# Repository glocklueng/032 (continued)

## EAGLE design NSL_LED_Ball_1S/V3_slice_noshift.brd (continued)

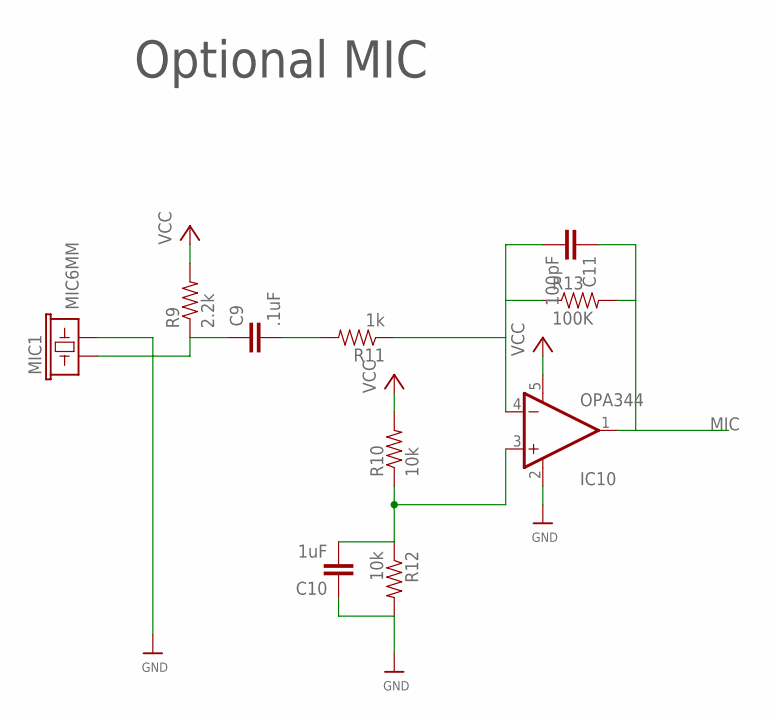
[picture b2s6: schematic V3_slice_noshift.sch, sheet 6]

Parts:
C9: .1uF; 0805
C10: 1uF; 0805
C11: 100pF; 0805
IC10: OPA344; SOT23-5
MIC1: MIC6MM; MIC-6MM
R9: 2.2k; 0805
R10, R12: 10k; 0805
R11: 1k; 0805
R13: 100K; 0805

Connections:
GND: C10.1, IC10.2 (V-), MIC1.2, R12.2; also elsewhere on the board
MIC: C11.1, IC10.1 (OUT), R13.2; also elsewhere on the board
unnamed: C9.2, R11.2
unnamed: C11.2, IC10.4 (-IN), R11.1, R13.1
unnamed: C9.1, MIC1.1, R9.1
unnamed: C10.2, IC10.3 (+IN), R10.1, R12.1
VCC: IC10.5 (V+), R9.2, R10.2; also elsewhere on the board

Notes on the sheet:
Optional MIC

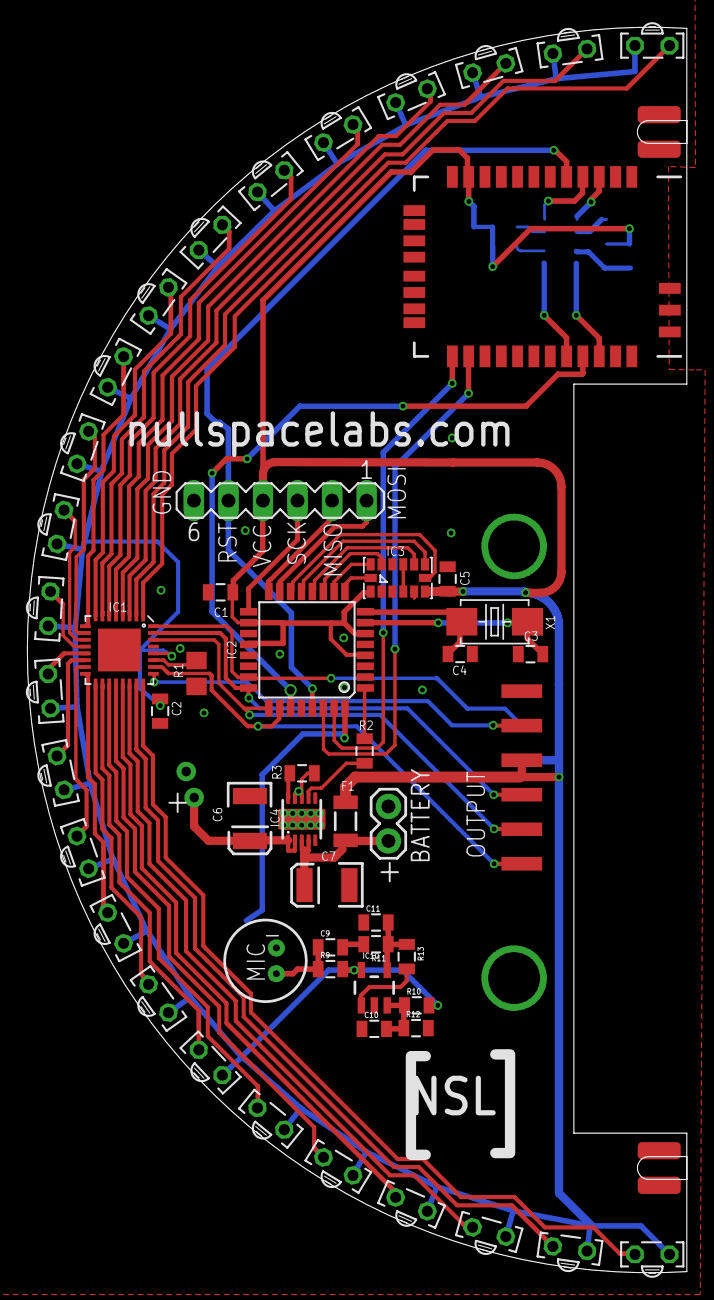
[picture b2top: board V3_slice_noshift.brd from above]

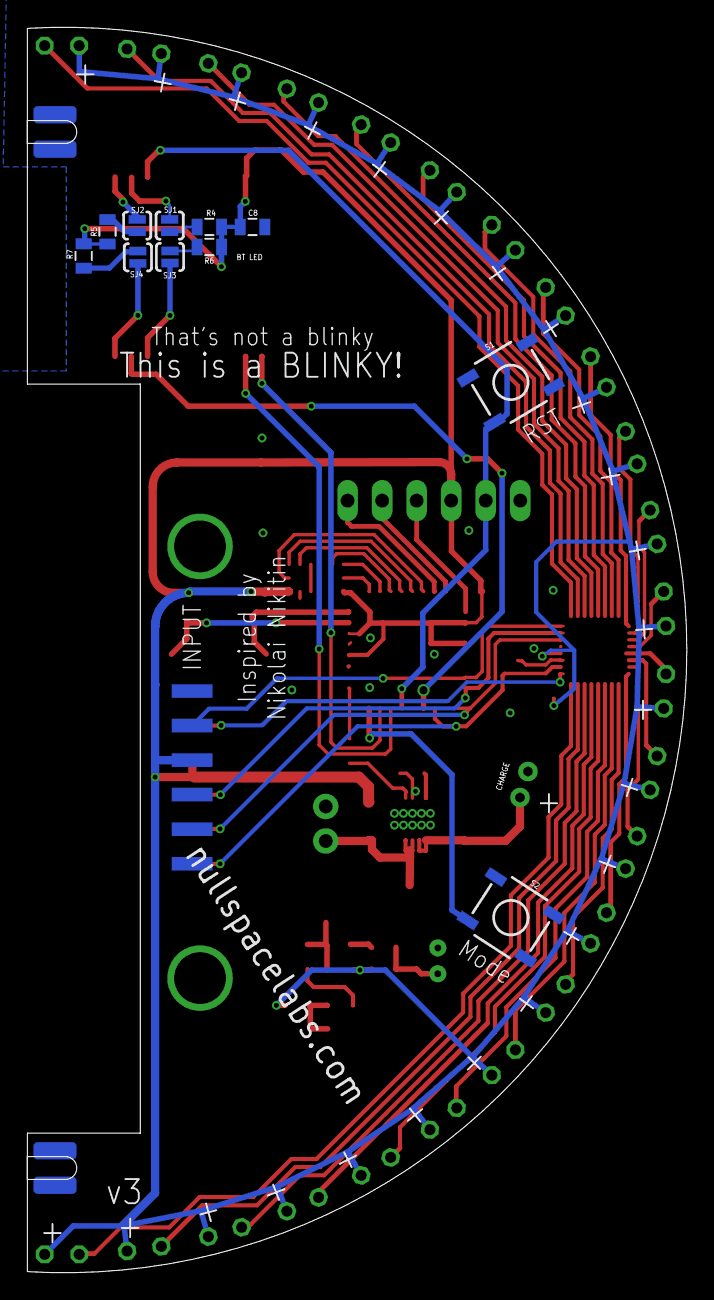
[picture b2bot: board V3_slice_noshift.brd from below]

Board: 2 copper layers, 48.5 x 91.6 mm, 69 parts (13 on the bottom side), 66 nets.

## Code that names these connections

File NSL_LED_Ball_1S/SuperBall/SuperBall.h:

#ifndef _RF_BLINKY_H_
#define _RF_BLINKY_H_ ( 1 )

// includes

#include <avr/io.h>
#include <util/delay.h>
#include <avr/interrupt.h>
#include <avr/sfr_defs.h>


#include <math.h> 
#include <avr/eeprom.h>
#include <avr/sleep.h>
#include <avr/power.h>
#include <avr/pgmspace.h>

#include <stdlib.h>
#include <string.h>

#include <math.h>


// typedefs

typedef unsigned char uchar;
typedef unsigned int uint;

// structures

// defines

#define SUPERBALL_WIDTH			(24)
#define SUPERBALL_HEIGHT		(16)

#define NUM_TLC5947 ( 16 )

#define bit_set(reg, bit) reg |= 1 << bit 
#define bit_clr(reg, bit) reg &= ~(1 << bit) 

#define SWSPI_PORT PORTD
#define SWSPI_DIR  DDRD
#define SWSPI_IN   PIND

#ifndef TWO_PI
#define TWO_PI 				( 6.283185307f )
#endif

#define SWSPI_SS   (1<<1) // (CSn of the SPI can also be connected to GND permanently.) 
#define SWSPI_SCK  (1<<2)  // CLK  SCL/SPC clock signal 
#define SWSPI_MOSI (1<<4)  // mosi sda/sdi/sdo master out,slave in PD2 
#define SWSPI_MISO (1<<4)  // miso SDO



#define DATPORT PORTC
#define CLKPORT PORTC //pc1
#define LATPORT PORTC
#define DATDDR DDRC

#define DATPIN PC0	//	SIN
#define CLKPIN PC1
#define BLANKPIN PC2
#define LATPIN PC3

#define SIN_PIN		_BV( PC0 ) /// PC0
#define SCLK_PIN	_BV( PC1 ) /// PC1
#define BLANK_PIN	_BV( PC2 )    /// PC2
#define XLAT_PIN	_BV( PC3 ) /// PC3


extern uint16_t LEDChannels[(NUM_TLC5947*24)];
extern unsigned char brightnessShift;
extern int gCount;

// prototypes

void USART_init(void);
unsigned char USART_receive(void);
void USART_send( unsigned char data);
void USART_putstring(char* StringPtr);
void SetPoint( unsigned short x, unsigned short y,unsigned short val);
void Clear(unsigned short val);
void Line( int x,int y,int x1,int y1);
void sleep_down( void );

// TLC
void WriteLEDArray(unsigned int count);
void LEDscan(int red, float degreeoffset,unsigned int count);
void LEDscan2(int red, float degreeoffset,unsigned int count);
void LEDscan3(int red, float degreeoffset,unsigned int count);
void LED_Init(void);
void LEDscan2Add(int red, float degreeoffset,unsigned int count);

//sw spi
void SWSPI_init();
void SWSPI_write( uint8_t address, uint8_t value );
uint8_t SWSPI_read( uint8_t address );




#endif

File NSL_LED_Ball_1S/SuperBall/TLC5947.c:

#include "SuperBall.h"


// Modified version of Garrett's octobrite code


// For octobrite code


uint16_t LEDChannels[(NUM_TLC5947*24)];

void SetPoint( unsigned short x, unsigned short y,unsigned short val)
{
	LEDChannels[ (  x * SUPERBALL_WIDTH ) + ( SUPERBALL_HEIGHT - y ) ] = val;
}

// 0.4095
void Clear(unsigned short val)
{

    for(unsigned short LEDindex = 0; LEDindex < (NUM_TLC5947  * 24); LEDindex++)
	{
      LEDChannels[LEDindex] = val;
    }
}

unsigned char brightnessShift= 0;


extern unsigned char chargeMode ;

//------------------------------------------------------------------------------------------
// Read all bits in the LEDChannels array and send them on the selected pins
//------------------------------------------------------------------------------------------
void WriteLEDArray(unsigned int count) {

  unsigned short tempOne = 0;

  for (unsigned int i = 0; i < (count  * 24); i++) {

    tempOne = LEDChannels[i]>>brightnessShift;
	
	// this limits the current draw during charging
	if( chargeMode ){
		tempOne >>= 3;
	}

    for (int j = 0; j < 12; j++) {
      if ((tempOne >> (11 - j)) & 1) {
        DATPORT |= (1 << DATPIN);
      } 
      else {
        DATPORT &= ~(1 << DATPIN);
      }

      CLKPORT |= (1 << CLKPIN);
      CLKPORT &= ~(1 << CLKPIN); 

    } 
  }

  LATPORT |= (1 << LATPIN | 1 << BLANKPIN);
  LATPORT &= ~(1 << LATPIN | 1 << BLANKPIN);
}

//------------------------------------------------------------------------------------------
// Sample function to draw a scanning pattern with fading
//------------------------------------------------------------------------------------------
void LEDscan(int red, float degreeoffset,unsigned int count) 
{

  float brightnessfactor = 0.0f;
  
  float scanindex = (1.0f + sinf(degreeoffset*3.14159f/180.0f)) * ((float)(NUM_TLC5947 * 24 ) / 2.0);
  
    for(unsigned int LEDindex = 0; LEDindex < (NUM_TLC5947  * 24); LEDindex++) {
      

      brightnessfactor = expf(0.0f - fabs(scanindex - ((float)LEDindex + 0.5f)) * 1.3f);

      LEDChannels[LEDindex] = red * brightnessfactor;
    }
    
    WriteLEDArray(count);  
}

void LEDscan2(int red, float degreeoffset,unsigned int count) 
{

  float brightnessfactor = 0.0f;
  
  float scanindex = (1.0f + sinf(degreeoffset*3.14159f/180.0f)) * ((float)(count * 24 ) / 2.0);
  
    for(unsigned int LEDindex = 0; LEDindex < (count  * 24); LEDindex++) {
      

      brightnessfactor = expf(0.0f - fabs(scanindex - ((float)LEDindex + 0.5f)) * 1.3f);

      LEDChannels[LEDindex] = red * brightnessfactor;
    }
}

void LEDscan2Add(int red, float degreeoffset,unsigned int count) 
{

  float brightnessfactor = 0.0f;
  
  float scanindex = (1.0f + sinf(degreeoffset*3.14159f/180.0f)) * ((float)(count * 24 ) / 2.0);
  
    for(unsigned int LEDindex = 0; LEDindex < (count  * 24); LEDindex++) {
      

      brightnessfactor = expf(0.0f - fabs(scanindex - ((float)LEDindex + 0.5f)) * 1.3f);

      LEDChannels[LEDindex] += red * brightnessfactor;

	  if( LEDChannels[LEDindex] > 4095 )  LEDChannels[LEDindex] = 4095;
    }
}


void LEDscan3(int red, float degreeoffset,unsigned int count) 
{

  float brightnessfactor = 0.0f;
  
  float scanindex = (1.0f + sinf(degreeoffset*3.14159f/180.0f)) * ((float)(count * 24 ) / 2.0);
  
    for(unsigned int LEDindex = 0; LEDindex < (count  * 24); LEDindex++) {
      

      brightnessfactor = expf(0.0f - fabs(scanindex - ((float)LEDindex + 0.5f)) * 1.3f);

      LEDChannels[LEDindex] = 4096-(red * brightnessfactor);
    }    
}

//------------------------------------------------------------------------------------------
// Sets up TLC5947 and MMA7455
//------------------------------------------------------------------------------------------
void LED_Init(void)
{

 // Setup TLC5947 pins
	DATDDR	|= ( SIN_PIN |SCLK_PIN|BLANK_PIN | XLAT_PIN );
	DATPORT	|= ( SIN_PIN |SCLK_PIN|BLANK_PIN | XLAT_PIN );
	
	DATPORT &= ~(LATPIN);
	DATPORT &= ~(BLANK_PIN);

	// setup button and charging indicator
	DDRC &=~(_BV(PC4)| _BV(PC5));
	PORTC |= _BV(PC4);
	PORTC |= _BV(PC5);

	// turn off ADC
	ADCSRA = 0;  

	// full bright	
	brightnessShift = 0;

	// clear the array
	memset(LEDChannels,0,sizeof(LEDChannels)*sizeof(uint16_t));

	// push off empty, do this before the sleep setup
	WriteLEDArray(NUM_TLC5947);

#if 0
	set_sleep_mode (SLEEP_MODE_PWR_DOWN);  
	sleep_enable();

	// turn off brown-out enable in software
	MCUCR = _BV (BODS) | _BV (BODSE);
	MCUCR = _BV (BODS); 
	sleep_cpu ();  

	// cancel sleep as a precaution
	sleep_disable();
#endif
}

// from
// http://www.gammon.com.au/forum/?id=11497

void sleep_down( void )
{
	set_sleep_mode (SLEEP_MODE_PWR_DOWN);  
	sleep_enable();

	// turn off brown-out enable in software
	MCUCR = _BV (BODS) | _BV (BODSE);
	MCUCR = _BV (BODS); 
	sleep_cpu ();  

}
